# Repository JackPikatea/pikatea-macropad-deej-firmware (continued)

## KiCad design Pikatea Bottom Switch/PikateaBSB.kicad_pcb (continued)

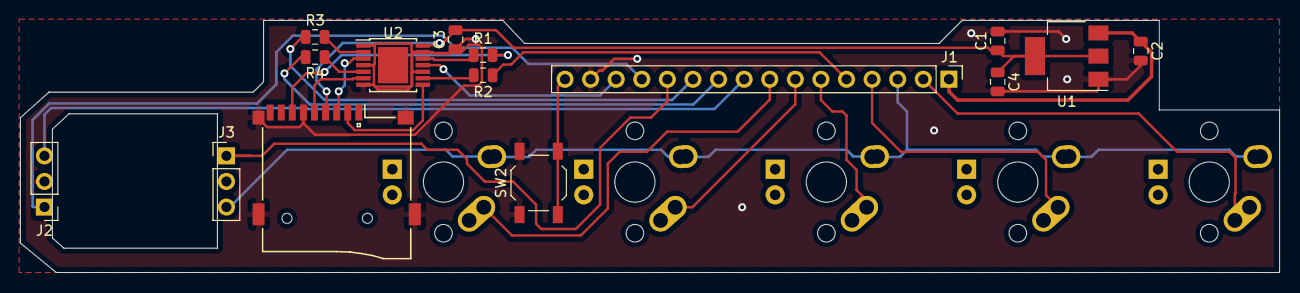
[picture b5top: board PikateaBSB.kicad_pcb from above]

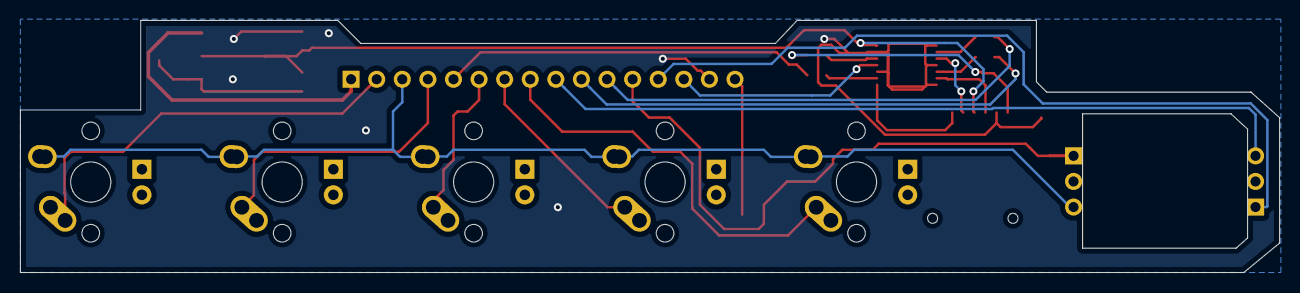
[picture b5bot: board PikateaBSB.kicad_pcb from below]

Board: 2 copper layers, 125.0 x 25.0 mm, 20 parts (5 on the bottom side), 25 nets.

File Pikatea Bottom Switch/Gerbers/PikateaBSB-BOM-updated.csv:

Pikatea-DB3,,,,,,,,,,
Item,Manufacturer,Manufacturer Part Number,Designator,Qty,Description,Package / Case,"SMD ,BGA,LLC(QFN),OR TH",Top/Bottom,X-Ray,Polarity
1,Yageo,CC0805KRX7R9BB104,"C1, C2, C4",3,"100nF,50V,10%,X7R,0805",805,SMD,T,,
2,Samsung Electro-Mechanics,CL21A106KAYNNNE,C3,1,"10uF,25V,10%,X5R,0805",805,SMD,T,,
3,UniOhm(??),0805W8F3301T5E,"R1, R2, R3, R4",4,"3.3K,1%,1/8W,0805",805,SMD,T,,
4,AMS,AMS1117-3.3,U1,1,"AMS1117-3.3,SOT-223",SOT-223,SMD,T,,Yes
5,Nxp Semiconductors,"74LVC125APW,118",U2,1,"74LVC125APW,118,14-TSSOP",14-TSSOP,SMD,T,,Yes
6,Taobao(??/????),PikateaDB2-SD,XS1,1,"Micro SD,14.75mmL*14.50mmW*1.85mmH",14.75mmL*14.50mmW*1.85mmH,TH,,,
